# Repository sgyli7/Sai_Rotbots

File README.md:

# Sai_Rotbots

面向真实世界互动与任务的开源机器人工程。保留轮腿机器人 **Sai_Agent_001**、后备箱平整的 **Sai_Agent_002**，并开发 **Goose V0.2** 与大型双足双手机器人 **Gorilla V0.1**。仓库由 `Sai_Agent_001` 直接改名，提交历史、Goose V0.1 与旧版本发布均保留。

| Robot | Cargo bay | Guide |
|---|---|---|
| Sai_Agent_001 | Original powered opposed pads and belt mechanism | [001](robots/Sai_Agent_001/README.md) |
| Sai_Agent_002 | Continuous flat floor, no moving clamp mechanism | [002](robots/Sai_Agent_002/README.md) |
| Goose_V0.1 | Long-neck biped with a gripping beak; initial training checkpoint | [Goose](robots/Goose_V0.1/README.md) |
| goose_v0_2 | Frozen15 training I/O; 061 complete native CAD candidate, appearance and assembly rejected | [Goose V0.2](robots/goose_v0_2/README.md) |
| gorilla_v0_1 | AA3 appearance; C15 segmented-foot stage, physical gates open | [Gorilla](robots/gorilla_v0_1/README.md) |

## Goose V0.2：038 原生检查点，整机仍未通过

本轮将最大圆冠限定在真实关节所需的40毫米轴段，前后收回低鞋轮廓，并重排小腿接管分界、退役两组旧罩专用紧固栈。**整机没有完成验收：踝侧摆两端各仍相交约4.8201 mm³，小腿横阶和工作口、原髋部及颈部活动问题仍未闭合。** 不作为完成外观、制造或新训练机体发布。

[完整原生BREP（XZ）](robots/goose_v0_2/cad/exports/tangpa_form_rebaseline_061/whole_checkpoint_038/goose_061_complete_native.brep.xz) · [全部输入与相对重建源包](robots/goose_v0_2/cad/source/tangpa_form_rebaseline_061/whole_checkpoint_038/archive_download.md) · [实际验收与未决](robots/goose_v0_2/evidence/tangpa_form_rebaseline_061/whole_checkpoint_038/owner_closeout_review.json) · [文件哈希](robots/goose_v0_2/evidence/tangpa_form_rebaseline_061/whole_checkpoint_038/package_manifest.json)

原生包已独立重导入核对1982实体、54,918面，171份输入SHA一致。该结果只证明制品可重建。冻结15的108个文件哈希保持；本轮未覆盖其质量、惯量、碰撞和执行器，也未启动训练。

[038实际斜视，拒绝记录](robots/goose_v0_2/images/tangpa_form_rebaseline_061/whole_checkpoint_038/whole_oblique.png) · [内侧近景](robots/goose_v0_2/images/tangpa_form_rebaseline_061/whole_checkpoint_038/whole_inner_leg_detail.png) · [机器人导航](robots/goose_v0_2/README.md)

## Gorilla V0.1：AA3 外形与复合脚阶段

Gorilla 以用户确认的 AA3 四视图为唯一外观基准，原图比例优先、高度暂取 2.65 m；目标是双足移动、双手操作与自主复杂任务。当前 [C15 阶段基底](robots/gorilla_v0_1/design/appearance_c15_stage.md)保存实际外壳、有限壁厚主框架和分段前掌/足弓/后跟；已提供同源可编辑模型、七机位实渲及有界几何检查。

这是一份可回退的探索候选，外观、完整内部装配、锁止承力和稳定物理合同仍未放行。历史 B 的运行模型与 C15 显示几何分别保留版本；Gorilla 不使用现有轮腿控制器或策略，Bevy 原生物理任务尚待后续验证。下一阶段先闭合真实内部模块的质量、空间、输出、供电与热预算，再细化壳体。

## Goose V0.1：一只幽默又实用的机器人鹅

Goose 的初衷来自 [Untitled Goose Game](https://goose.game/)：把鹅的好奇、探头、歪头、回望、动作停顿和叫声带进真实世界，也让它能帮人做小事。**叼起物品和拖拽物体同等重要**；目标包括指定轻量日用品、布边、空拖鞋、轻篮及小车，支持遥控和“叼过来／拖到指定位置／放下”的指定物自主任务。这些是设计目标，完整任务能力仍待验证。

我们将它视作 [MicroDuck](https://github.com/pollen-robotics/microduck) 的“Max Pro”方向：借鉴双足互动机器人的经验，增加头颈活动范围、真实嘴部夹持和腿脚机动。外观追求简约的鹅感，以可打印曲面、大眼、橙色嘴脚和两侧手动检修门表达角色；检修门不画写实羽毛。最终外观须与实际制造装配一一对应。

### 当前工程装配

上图直接来自当前 **478 件候选源装配**，不是实物照片或最终制造验收图。单件打印主头壳、相机面板、夹嘴和深色承力结构分别承担实际功能。当前候选有 **18 个主动轴、约 10.40 kg 条件质量**；闭合零位包围尺寸约 **43.4 × 26.7 × 64.2 cm**（长 × 宽 × 高），姿态变化会改变外部包围尺寸。质量含设计预留，尚非实物称重。两侧检修门已加入实际手动铰链和关闭保持；上沿接缝和外露支臂仍待最终审美与制造资格。

| Cream 奶油白 | Graphite 石墨灰 |
|---|---|
|  |  |
| Lavender 薰衣草紫 | Sky 天空蓝 |
|  |  |

四款使用同版几何、同镜头与灯光，分别配置主壳、中性检修门／脸板、深色骨架、嘴脚及眼圈／鞋边辅色；见[配色与源身份记录](robots/Goose_V0.1/design/manual_wing_service_checkpoint.md)。

### 设计图与外观演进

| 早期 R2 尖嘴概念 | 已确认的阶段性外观基线 |
|---|---|
|  |  |

这些图保留设计意图和演进过程。右侧[外观基线](robots/Goose_V0.1/design/fuller_exterior_review.md)曾获阶段性确认；之后按真实器件、承力和装配需求继续调整。概念图上的旧尺寸与性能不作为当前工程参数，当前手动翼门候选仍需最终审美与制造验收。

### 当前交付与下一步

**直接查看：[优化后的11碰撞体示意图](robots/Goose_V0.1/images/task_proxy_11_v1_colliders.png) · [碰撞体文件目录](robots/Goose_V0.1/models/task_proxy_11_v1/)。**

当前 Sim2Sim 入口是[11 个碰撞体的任务代理](robots/Goose_V0.1/design/task_proxy_11_v1.md)，绑定[同版入口与契约](robots/Goose_V0.1/configs/task_proxy_11_v1_entry.json)。硬件 CAD、打印源、BOM、质量与完整惯量保持独立；MuJoCo 与原生 Rapier 各完成 2,500 次实际积分，通过冷启动、站立、有限关节动作、嘴部行程和负载／摩擦检查。18 项动作、65 项基础观测及 82 项指定物扩展可供 Sai_Lab 绑定新策略；这不代表已学会行走、转向、拾取／拖拽或适应复杂地面。Godot/Jolt、Unity 仍需各自验证。

当前[478件结构检查点](robots/Goose_V0.1/design/manual_wing_service_checkpoint.md)有独立CAD/SI与采购增量；003运行模型继续绑定原来的10.430690821kg参数，不混用新版硬件质量。[精确驱动资料及18轴端点](robots/Goose_V0.1/hardware/power_release_checkpoint.md)已补齐电压、插头及型号协议范围；新增[绝对阈值制动电路候选](robots/Goose_V0.1/hardware/absolute_brake_chopper_checkpoint.md)通过原生连通、条件角点和实际NGSPICE行为/故障对照，仍未取得PCB、热与完整安装资格。完整安装与线束、翼门连续开合和接缝、供电保护和独立急停、真实电机额定及热／载荷检查仍未闭合，**不能直接按候选 BOM 下单装机；第三、第四阶段和硬件冻结尚未完成**。原交接图片、文档、采购表以及成功／失败记录均保留，历史模型的结果不替代当前版本验证。

后续[制动安装比较](robots/Goose_V0.1/hardware/brake_packaging_checkpoint.md)补上48件独立CAD增量、525件装配源和10.486951740kg条件参数，并复查有限转向／低姿态与同版静力。它保留PCB、热／工具／线束和连续扫掠门槛；运行模型继续使用003的11个凸碰撞体。

从[Goose 资料入口](robots/Goose_V0.1/README.md)、[新版独立接收器与复测命令](integrations/bevy/goose_task_proxy/README.md)、[历史 460 件训练交接](robots/Goose_V0.1/design/training_checkpoint_handoff.md)、[单件头壳结构](robots/Goose_V0.1/design/one_piece_head_checkpoint.md)、[行为要求](robots/Goose_V0.1/design/behavior_requirements.md)继续；[原始资料图片库](robots/Goose_V0.1/design/concepts/index.html)与[导入记录](robots/Goose_V0.1/source/workspace_import.md)保留溯源。大型 Blender／OBJ 资产须按 [Git LFS 拉取说明](docs/guides/large_asset_checkout.md)获取完整内容。

## Project organization

Robot-specific design, models and evidence live under `robots/<robot_id>/`.
Shared policies and configurations live under `shared/`; common software lives
under `src/sai_agent/`, with categorized command entrypoints in `scripts/`.
Local generated runs belong in `artifacts/<robot_id>/<run_id>/` and are not committed.

Read the [engineering rules](sai_robots_engineering_rules.md) before adding or
moving files. The [migration record](docs/guides/directory_migration.md) maps old
paths to their new locations without rewriting historical experiment records.

Both variants retain the front SO101 arm, four wheel-legs, camera mounts and
rear touchscreen layout. Hardware has not been built or calibrated.

## Run in Godot

Python 3.12, Godot 4.7.2 and `uv`:

```sh
uv sync
uv run sai-agent godot --robot Sai_Agent_002
uv run sai-agent godot --robot Sai_Agent_001
```

W/S 前进后退，A/D 左右转向，按住 Shift 下蹲、松开恢复，R 重启。
Omitting `--robot` preserves the original 001 default.

```sh
uv run sai-agent godot --robot Sai_Agent_002 --task cargo
uv run sai-agent godot --robot Sai_Agent_002 --stairs .04
```

002 uses contact-only pickup → placement → passive transport. It has no
clamping stage or cargo attachment constraint. Objects can slide or fall;
this variant does not promise automatic load restraint. Camera images are
available but the current tasks use model-state IK and terrain raycasts,
not VLA. The touchscreen remains a hardware layout, not implemented firmware.

## Models, training and integrations

[`robots/catalog.json`](robots/catalog.json) maps stable robot IDs to separate
model directories. Shared controllers/policies are retained; new robots can add
catalog entries and their own model directory. The `sai-agent-001` Python
package name and `sai_agent` import remain for existing integration compatibility.
The repository name is `Sai_Rotbots` as requested, including that spelling.

```sh
uv sync --extra test --extra cad --extra assets --extra hardware
uv run pytest -q
uv run python scripts/evaluation/evaluate_flat.py --robot Sai_Agent_002 --policy shared/policies/flat-v1.onnx --full-robot --out artifacts/002-flat --require-pass
uv run --extra train python scripts/training/train.py --robot Sai_Agent_002 --worlds 256 --seconds 300 --name my-002-trial
```

The variant reuses existing trained actors and is checked on its changed
mass/contact model. It is not presented as a newly trained policy. GPU training
accepts `--robot`; each run records the selected model hash and robot ID.

See [002 scope and evidence](robots/Sai_Agent_002/README.md),
[game integration notes](docs/guides/integrations.md),
[001 historical acceptance](robots/Sai_Agent_001/design/simulation_guide.md),
[variant plan](robots/Sai_Agent_002/design/agent_002_plan.md), and [third-party notices](THIRD_PARTY_NOTICES.md).
Old alpha.3 results describe 001, not 002. Unity editor validation remains pending.

SO101 and Raspberry Pi derivatives retain their upstream licenses. Supplier
CAD with unconfirmed redistribution rights is represented by independent
nominal display envelopes. Physics parameters are documented estimates, not
measured hardware values. Inspired by [MicroDuck](https://github.com/pollen-robotics/microduck)'s
functional design philosophy; the wheel-leg cargo chassis is an independent design.

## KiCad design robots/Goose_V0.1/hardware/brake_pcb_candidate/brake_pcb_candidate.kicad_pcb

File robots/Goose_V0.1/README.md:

# Goose V0.1

一只幽默又实用的双足机器人鹅：长颈、嘴内夹持、手动翼形检修门。设计参考 Untitled Goose Game 与 MicroDuck；叼取和拖拽同等重要。

## 碰撞体优化交付

**当前版本：`goose_task_proxy_11_v1`，共11个凸碰撞体。**

| 你要找的内容 | 直接打开 | 文件内容 |
|---|---|---|
| **1. 碰撞体示意图** | [打开三视图 PNG](images/task_proxy_11_v1_colliders.png) | 下方同图：斜视、侧视、正视，以及11个碰撞体的颜色图例 |
| **2. 碰撞体文件** | [打开碰撞文件目录](models/task_proxy_11_v1/) · [装配模型 robot.xml](models/task_proxy_11_v1/robot.xml) | 11个OBJ凸包；XML定义位置与关节装配，native_plant.json保留原硬件参数 |

取用时保留整个文件目录。OBJ以米为单位、使用所属刚体的局部坐标；组装位置以`robot.xml`为准。**这是仿真碰撞代理，真实硬件CAD与打印件另行保存。**

[逐个OBJ文件清单、运行契约与验证说明](design/task_proxy_11_v1.md)。

## 其他当前资料

| 内容 | 入口 |
|---|---|
| 外观、手动检修门与硬件结构候选 | [实际四色图、CAD及采购增量](design/manual_wing_service_checkpoint.md) |
| 电气与制动PCB候选 | [可编辑原理图、PCB与验证范围](hardware/brake_pcb_checkpoint.md) |
| 指定物训练输入 | [圆柱抓杆／把手，100／200／300g](design/task_samples_v1_handoff.md) |
| 虚拟训练版本与后续硬件差异 | [004冻结说明](design/virtual_training_freeze_handoff.md) |

硬件资料属于独立候选，未替换上述碰撞版本。平地工程入口、完整动作任务、各游戏引擎和实体制造分别验收；具体范围见各入口。

<details>
<summary>历史记录与原始导入资料</summary>

[历史记录与阶段候选](design/history_index.md)。旧模型、旧图、聊天交接和阶段试验集中从此页查阅，不作为当前碰撞交付入口。

</details>

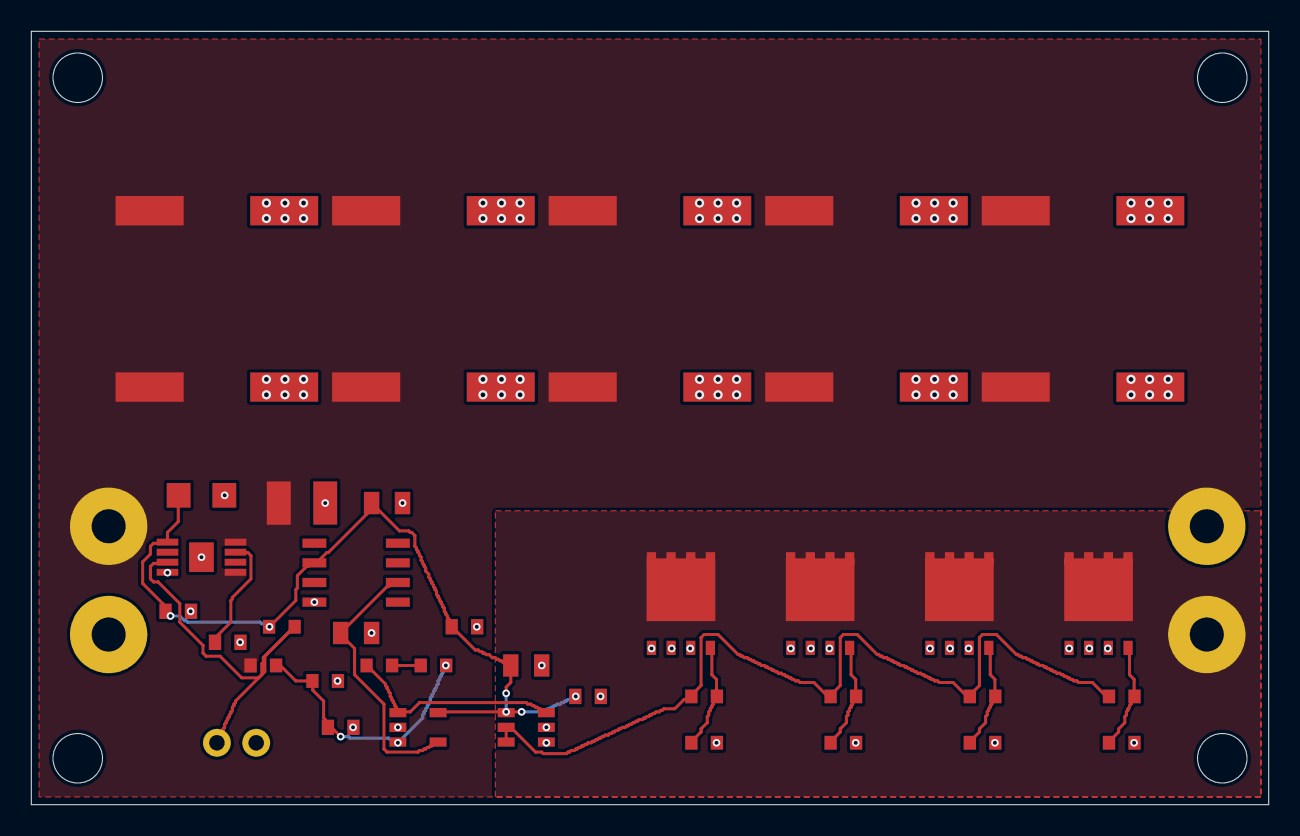
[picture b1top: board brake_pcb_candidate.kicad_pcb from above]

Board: 2 copper layers, 80.0 x 50.0 mm, 48 parts (0 on the bottom side), 15 nets.

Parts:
C1, C2, C3, C4, C5, C6, C7, C8, C9, C10: 35SVPF120M; panasonic_f12
C11: 10 uF; c1210
C12: 10 uF; c1206
C13, C18, C19: 0.1 uF; c0603
C14, C16, C17: 1 uF; c0805
C15: 0.0001 uF; c0603
C20: 0.01 uF; c0603
H1, H2, H3, H4: mount_hole_32
J1: protected motor bus solder pads; paired_wire_terminal_7mm
J2: brake resistor solder pads; paired_wire_terminal_7mm
J3: bias ready monitor; pg_monitor_2p_254
Q1, Q2, Q3, Q4: BSC027N06LS5; bsc027n06ls5_pg_tdson8
R1: 100000 ohm; r0603
R2: 10700 ohm; r0603
R3, R31: 825000 ohm; r0603
R4: 10000 ohm; r0603
RG1, RG2, RG3, RG4: 2.2 ohm; r0603
RP1, RP2, RP3, RP4: 100000 ohm; r0603
U1: TPS7A1650DGNR; tps7a1650_dgn0008c
U2: REF5025IDR; ref5025_d0008a
U3: TLV3201DBVR; ti_dbv0005a
U4: UCC27511DBVR; ti_dbv0006a

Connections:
BIAS_5V: C12.1, C13.1, C16.1, C17.1, C18.1, C19.1, R4.1, U1.1, U2.2, U3.5, U4.1
BIAS_PG: J3.1, R4.2, U1.3
BIAS_PG_DELAY: C20.1, U1.7
BRAKE_REQUEST: R3.1, U3.1, U4.6
BUS: C1.1, C2.1, C3.1, C4.1, C5.1, C6.1, C7.1, C8.1, C9.1, C10.1, C11.1, J1.1, J2.1, R1.1, U1.5, U1.8
FEEDBACK_MID: R3.2, R31.1
GATE1: Q1.4, RG1.2, RP1.1
GATE2: Q2.4, RG2.2, RP2.1
GATE3: Q3.4, RG3.2, RP3.1
GATE4: Q4.4, RG4.2, RP4.1
GATE_DRIVE: RG1.1, RG2.1, RG3.1, RG4.1, U4.2, U4.3
GND: C1.2, C2.2, C3.2, C4.2, C5.2, C6.2, C7.2, C8.2, C9.2, C10.2, C11.2, C12.2, C13.2, C14.2, C15.2, C16.2, C17.2, C18.2, C19.2, C20.2, J1.2, J3.2, Q1.1, Q1.2, Q1.3, Q2.1, Q2.2, Q2.3, Q3.1, Q3.2, Q3.3, Q4.1, Q4.2, Q4.3, R2.2, RP1.2, RP2.2, RP3.2, RP4.2, U1.4, U1.9, U2.4, U3.2, U4.4, U4.5
REF_2V5: C14.1, U2.6, U3.4
SENSE: C15.1, R1.2, R2.1, R31.2, U3.3
SW_RETURN: J2.2, Q1.5, Q1.6, Q1.7, Q1.8, Q2.5, Q2.6, Q2.7, Q2.8, Q3.5, Q3.6, Q3.7, Q3.8, Q4.5, Q4.6, Q4.7, Q4.8

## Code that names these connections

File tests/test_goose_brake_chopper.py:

import copy
import json
from pathlib import Path

import numpy as np
import pytest

from sai_agent.goose.brake_chopper import compare, threshold_voltage, validate_circuit

ROBOT = Path(__file__).resolve().parents[1] / "robots/Goose_V0.1"


def candidate():
    return json.loads((ROBOT / "configs/absolute_brake_chopper_candidate.json").read_text())


def test_threshold_kcl_independently_solved_as_two_node_network():
    # Unknowns are bus voltage and sense voltage; equations use conductances.
    for rt, rb, rf, ref, output, bias in [(100e3, 10700, 1.65e6, 2.5, 0, 0),
                                         (103e3, 10200, 1.7e6, 2.49, 4.8, 5e-9)]:
        matrix = np.array([[-1/rt, 1/rt + 1/rb + 1/rf], [0, 1]])
        solution = np.linalg.solve(matrix, [output/rf - bias, ref])
        assert threshold_voltage(rt, rb, rf, ref, output, bias) == pytest.approx(solution[0], rel=1e-14)
        assert solution[1] == ref


@pytest.mark.parametrize("fault", ["upstream_bias", "fixed_ldo_dnc_grounded", "wrong_reference_grade",
    "reference_output_pin", "driver_inverted", "driver_pinout_other_variant", "fet_reversed",
    "cap_reversed", "wrong_cap_voltage_sku", "feedback_wrong_node", "threshold_wrong_value",
    "duplicate_ref", "pretend_release"])
def test_pin_and_domain_faults_rejected(fault):
    x = copy.deepcopy(candidate())
    parts = {c["ref"]: c for c in x["components"]}
    if fault == "upstream_bias":
        parts["U1"]["pins"]["8"]["net"] = "UPSTREAM_BATTERY"
    elif fault == "fixed_ldo_dnc_grounded":
        parts["U1"]["pins"]["2"]["net"] = "GND"
    elif fault == "wrong_reference_grade":
        parts["U2"]["sku"] = "REF5025AIDR"
    elif fault == "reference_output_pin":
        parts["U2"]["pins"]["5"]["net"] = "REF_2V5"
    elif fault == "driver_inverted":
        parts["U4"]["pins"]["5"]["net"] = "BRAKE_REQUEST"
    elif fault == "driver_pinout_other_variant":
        parts["U4"]["pins"]["1"]["net"] = "GND"
    elif fault == "fet_reversed":
        parts["Q1"]["pins"]["1"]["net"] = "SW_RETURN"
    elif fault == "cap_reversed":
        parts["C1"]["pins"]["1"]["net"] = "GND"
    elif fault == "wrong_cap_voltage_sku":
        parts["C1"]["sku"] = "16SVPF1000M"
    elif fault == "feedback_wrong_node":
        parts["R3"]["pins"]["1"]["net"] = "GND"
    elif fault == "threshold_wrong_value":
        parts["R2"]["value"] = "12000 ohm"
    elif fault == "duplicate_ref":
        x["components"].append(copy.deepcopy(parts["U1"]))
    elif fault == "pretend_release":
        x["hardware_enable_release"] = True
    with pytest.raises(ValueError):
        validate_circuit(x)


def test_comparison_keeps_assumptions_and_mass_gap_explicit():
    contract = json.loads((ROBOT / "configs/mechanical_physics_contract.json").read_text())
    result = compare(candidate(), contract)
    assert result["response"]["qualified_delay_s"] is None
    assert result["response"]["conditional_delayed_peak_v"] < 28
    assert result["full_6s_false_trigger_margin_v"] > 0
    assert result["dump_stage"]["ideal_peak_equilibrium_v_one_open"] < 28
    assert result["capacitors"]["derated_total_rating_a_10_to_100khz_equal_sharing"] == pytest.approx(30.8)
    assert result["mass"]["existing_total_protection_and_brake_reservation_kg"] == pytest.approx(.213)
    assert result["mass"]["remaining_before_pcb_capacitors_mounts_wires_kg"] == pytest.approx(.02948)
    assert result["mass"]["installed_complete_mass_kg"] is None
    assert result["hardware_enable_release"] is False


@pytest.mark.parametrize("delay", [50e-6, 100e-6])
def test_delayed_response_does_not_inherit_ideal_pass(delay):
    x = candidate()
    x["threshold"]["full_path_response_budget_s_assumed"] = delay
    contract = json.loads((ROBOT / "configs/mechanical_physics_contract.json").read_text())
    assert compare(x, contract)["response"]["conditional_delayed_peak_v"] > 28
